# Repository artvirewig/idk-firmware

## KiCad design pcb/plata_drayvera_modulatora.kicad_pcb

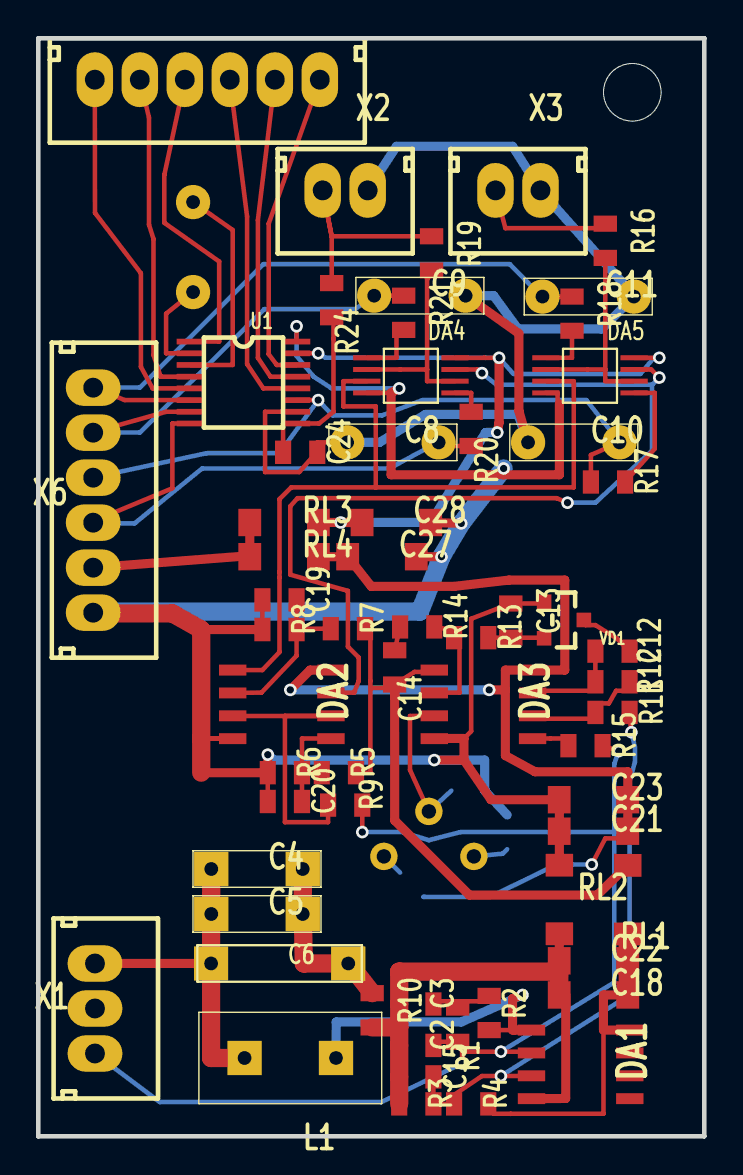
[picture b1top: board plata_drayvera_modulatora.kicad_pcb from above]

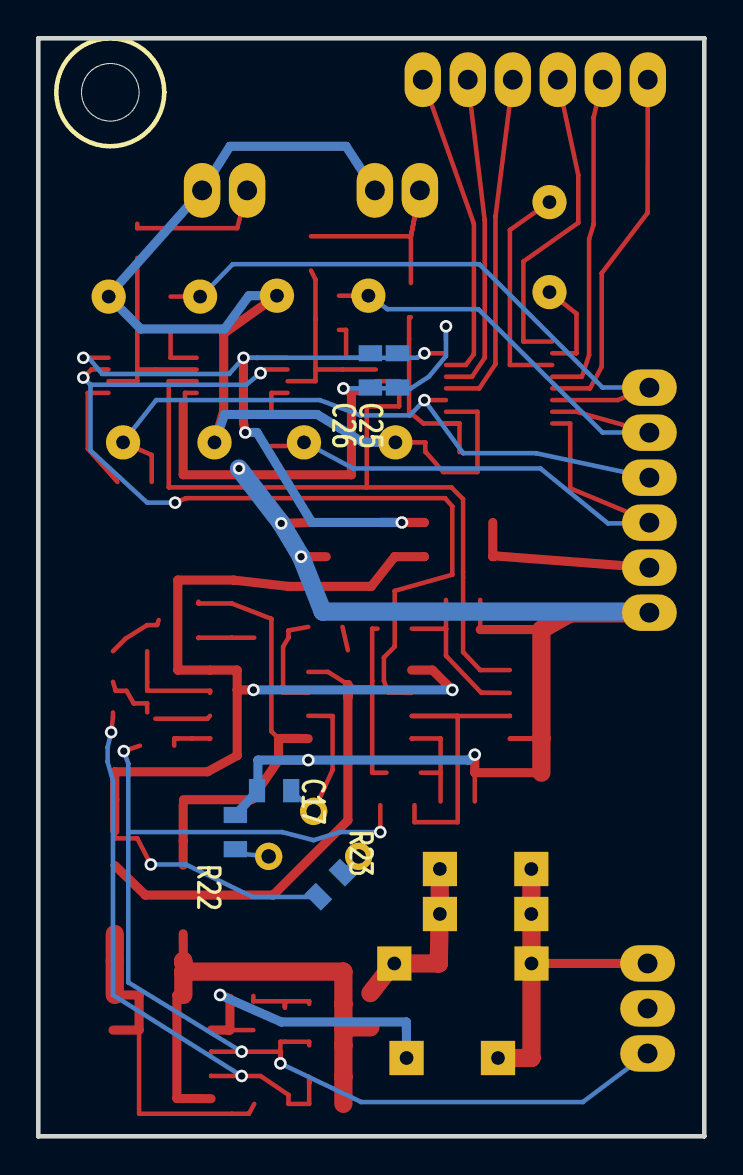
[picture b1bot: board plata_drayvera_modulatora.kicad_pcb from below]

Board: 2 copper layers, 37.0 x 61.0 mm, 66 parts (5 on the bottom side), 46 nets.

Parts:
C2, C14: 6n8; C0805_MINI_1
C3, C15, C17: 0.22; C0805_MINI_1
C4, C5, C8, C9, C10, C11: {Value}; C_1
C6: {Value}; C7_1
C12, C13, C19, C20, C24, C25, C26: 0.1; C0805_MINI_1
C18, C21, C22, C23, C27, C28: 10,0; C1206_1
DA1, DA3: AD8397_1_1
DA2: LMV762MA; AD8397_1_1
DA4, DA5: MAX4642_1
L1: RCH114NP-332KB; L-КИГ_1
R1, R24: 100k; R0805_MINI_1
R2: 51k; R0805_MINI_1
R3, R4, R5, R6, R7, R8, R9, R13, R14, R15, R16, R17, R18, R19, R20, R21, R22, R23: 1k; R0805_MINI_1
R10: 1R0; R0805_MINI_1
R11: 11k; R0805_MINI_1
R12: 22k; R0805_MINI_1
RL1, RL2, RL3, RL4: {Value}; R1206_1
U1: AD7705_1
VD1: BAT54S_1
X1: PW10-3-M_1
X2, X3: PW10-2-M_1
X5, X6: PW10-6M_1

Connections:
1:Z+I: R19.2, R24.1, X2.1
1_V+: C25.2, C26.2, C28.2, DA4.8, DA5.8, RL3.2, U1.15
2_V+: C21.1, C23.1, C27.2, DA2.8, DA3.8, R23.2, RL4.2
AGND: C8.1, C9.2, C10.1, C11.2, C24.1, U1.10, X2.2, X3.2
CS: U1.4, X5.2
DIN: U1.14, X5.6
DMD1+: C9.1, R21.2, U1.7, X6.5
DMD1-: C8.2, R20.2, U1.8, X6.3
DMD2+: C11.1, R18.2, U1.6, X6.6
DMD2-: C10.2, R17.2, U1.11, X6.4
DOUT: U1.13, X5.5
DRDY: U1.12, X5.4
GND: C13.2, C17.2, C19.2, C20.2, C21.2, C23.2, C25.1, C26.1, C27.1, C28.1, DA2.4, DA3.4, DA4.4, DA5.4, R6.1, R8.1, R22.2, RL2.2, U1.16, VD1.1, X6.1
HI_COMP: C20.1, DA2.5, R5.1, R6.2
LO_COMP: C19.1, DA2.2, R7.1, R8.2
NET00000: DA1.1, L1.1, R2.1
NET00001: C4.2, C5.2, C6.1, L1.2, X1.3
NET00002: C2.1, DA1.2, R1.2, R9.1, R15.1, X1.1
NET00003: C3.1, R1.1, R2.2
NET00005: C4.1, C5.1, C6.2, R10.2
NET00007: DA4.5, R20.1
NET00011: DA4.1, R21.1
NET00012: DA5.5, R17.1
NET00013: DA5.1, R18.1
NET00016: DA4.2, DA4.6, R19.1
NET00017: DA5.2, DA5.6, R16.1
NET00018: C12.1, DA3.7, R12.1
NET00019: C12.2, VD1.3
NET00020: C13.1, R13.1, VD1.2
NET00021: DA3.6, R11.2, R12.2
NET00022: DA3.2, R13.2, R14.1
NET00023: R16.2, X3.1
NET00024: C14.1, R14.2
NET00025: DA3.5, R15.2
NET00029: C14.2, DA3.1, R5.2, R7.2, RL1.1
NET00031: C24.2, R24.2, U1.9
REF_0: C15.1, DA1.3, R3.2, R4.1, R11.1
REF_PEM: C17.1, DA3.3
RESET: U1.5, X5.1
SCLK: U1.1, X5.3
SGND: C2.2, C3.2, C15.2, C18.2, C22.2, DA1.4, R3.1, R10.1, RL2.1
SIN_COMP: DA2.3, DA2.6, R9.2
SYNC_0: DA2.7, DA4.7, DA5.7
SYNC_1: DA2.1, DA4.3, DA5.3
V+: RL3.1, RL4.1, X6.2
V+REG: C18.1, C22.1, DA1.8, R4.2, RL1.2

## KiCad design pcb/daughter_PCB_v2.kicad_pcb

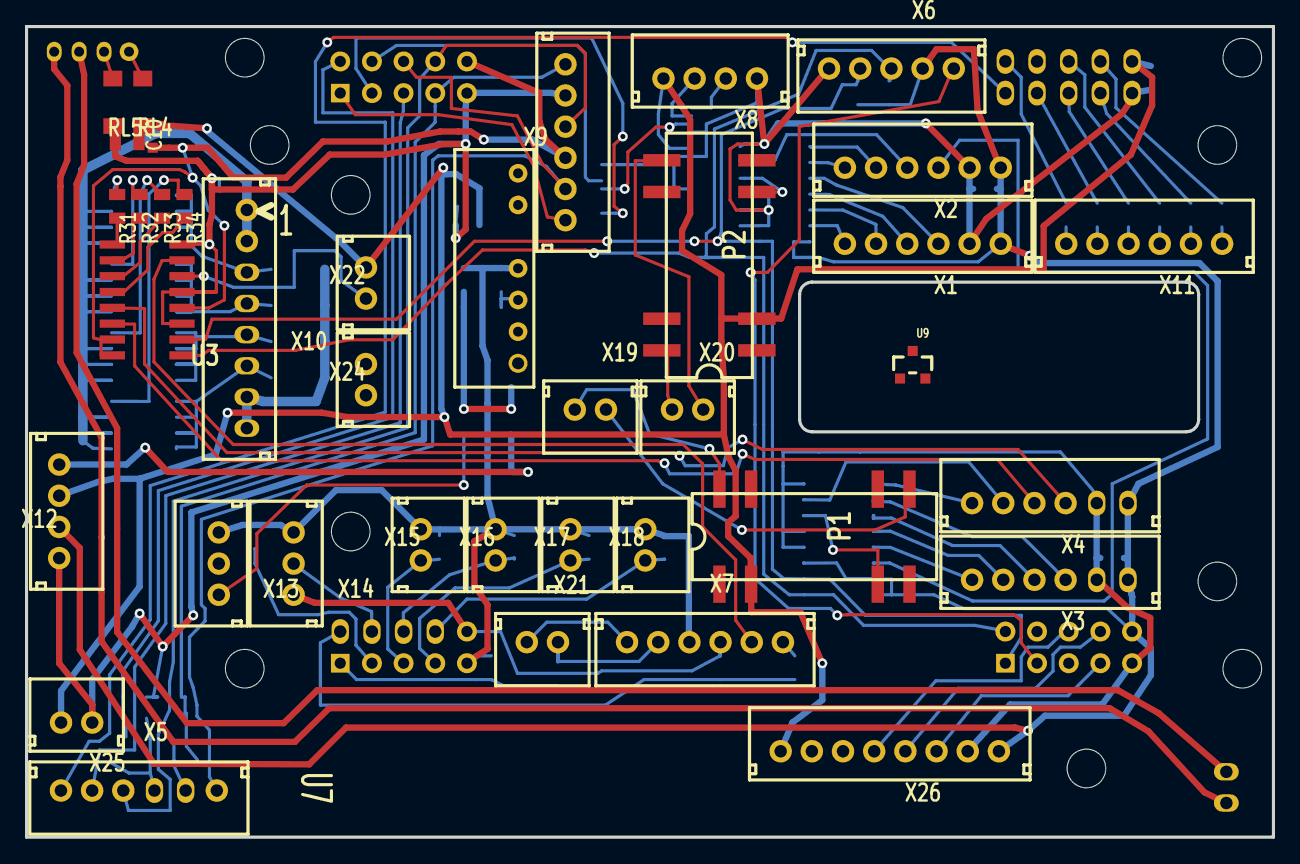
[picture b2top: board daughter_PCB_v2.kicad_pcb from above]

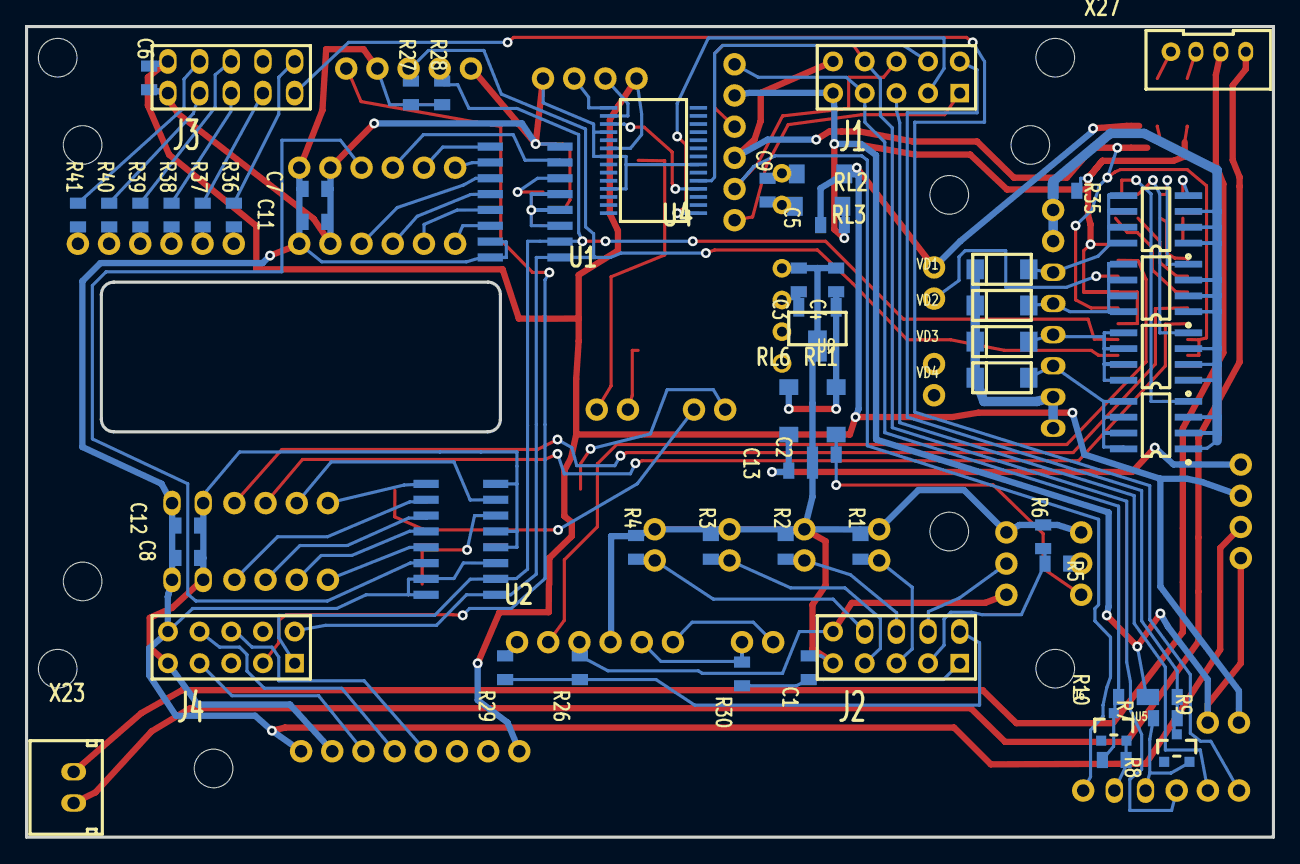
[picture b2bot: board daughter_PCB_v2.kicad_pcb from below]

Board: 2 copper layers, 100.0 x 65.0 mm, 95 parts (54 on the bottom side), 97 nets.

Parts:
C1, C2, C3, C4, C5, C6, C7, C8, C9, C10, C11, C12, C13: 0.22; C0805_MINI_1
J1, J2, J3, J4: PBD10_1
P1, P2: TRR1AS00D; TRR1A_1
R1, R2, R3, R4: k10; R0805_MINI_1
R5: 10k; R0805_MINI_1
R6, R27, R28, R36, R37, R38, R39, R40, R41: 3k3; R0805_MINI_1
R7, R8: 2k2; R0805_MINI_1
R9, R10: 4k7; R0805_MINI_1
R26: 300k; R0805_MINI_1
R29: 9M1; R0805_MINI_1
R30, R31, R32, R33, R34: 10K; R0805_MINI_1
R35: 10; R0805_MINI_1
RL1, RL2, RL3, RL4, RL5, RL6: 1206; R1206_1
U1, U2, U3: PCA9557_1
U4: FT232RL_1
U5, U6, U9: BAT54S_1
U7: {Value}; AMXD-XXXXD_1
U8: NJM78L09UA_1
VD1, VD2, VD3, VD4: VS-10MQ040; DIOD_SMA_1
VT1, VT2, VT3, VT4: IRF7416_1
X1: SERVO_1; PW10-6M_1
X2: SERVO_2; PW10-6M_1
X3: SERVO_3; PW10-6M_1
X4: SERVO_4; PW10-6M_1
X5: ADC; CONNECTOR_6_1
X6: BMP085; PW10-5-M_1
X7: PMT_BOARD; CONNECTOR_6_1
X8: USB; CONNECTOR_4_1
X9: SD card; PW10-6M_1
X10, X26: PW10-8M_1
X11: RESERVE; PW10-6M_1
X12: POWER IN; PW10-4-M_1
X13: Flow_sensor; PW10-3-M_1
X14: Cell T sensor; PW10-3-M_1
X15, X16, X17, X18, X19, X20, X21, X22, X23, X24, X25: PW10-2-M_1
X27: MU-4_1

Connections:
+: C10.1, RL4.2
+3.3: C7.1, C8.1, C11.1, C12.1, J1.10, J4.10, R27.2, R28.2, U1.15, U1.16, U2.3, U2.15, U2.16, U3.4, U3.15, U3.16, X1.1, X2.1, X3.1, X4.1, X6.4, X9.3, X12.2, X26.1
+5V: C5.1, C6.1, J3.10, P1.2, P2.2, RL2.1, U4.20, X8.4, X12.3, X22.2, X25.2, X26.8
+12: C13.1, RL6.2, X12.4
+12V: C4.1, RL1.1, RL6.1, U8.3
ADCA1: J3.2, R36.1
ADCA2: J3.3, R37.1
ADCB4: J3.5, R38.1
ADCB5: J3.6, R39.1
ADCB6: J3.7, R40.1
ADCB7: J3.8, R41.1
CLK: J1.8, X5.3, X9.4
CS_AD7705: J1.5, X5.2
CS_SD-CARD: J1.1, X9.1
DOUT_AD7705: R8.1, U6.2, X5.5
DRDY_AD7705: R7.1, U5.2, X5.4
GND: C1.2, C2.1, C3.2, C4.2, C5.2, C6.2, C7.2, C8.2, C10.2, C11.2, C12.2, C13.2, J1.9, J2.9, J3.9, J4.9, R1.1, R2.1, R3.1, R4.1, R6.1, R9.2, R10.2, R35.1, RL3.1, RL5.2, U1.3, U1.4, U1.5, U1.8, U2.4, U2.5, U2.8, U3.3, U3.5, U3.8, U4.7, U4.18, U4.21, U4.25, U7.4, U8.2, X1.2, X2.2, X3.2, X4.2, X6.1, X7.3, X8.1, X9.5, X12.1, X13.1, X14.1, X15.2, X16.2, X17.2, X18.2, X25.1, X26.2
IGN+: X23.1, X27.3
IGN-: X23.2, X27.4
IGNITION: U3.7, X7.5
L+: RL4.1, X27.1
L-: RL5.1, X27.2
MISO: J1.7, R8.2, R10.1, U6.3, X9.6
MOSI: J1.6, X5.6, X9.2
NET00000: R36.2, X11.6
NET00001: VD1.1, VD2.1, VD3.1, VD4.1, X10.7, X10.8
NET00002: C9.1, RL2.2, U7.1
NET00003: C9.2, RL3.2, U7.2
NET00004: R37.2, X11.5
NET00005: R38.2, X11.4
NET00006: C3.1, U7.5, U8.1
NET00007: R39.2, X11.3
NET00008: R40.2, X11.2
NET00009: R41.2, X11.1
NET00043: C1.1, J2.1, R30.1
NET00045: R5.1, X13.2
NET00046: J2.4, X14.2
NET00047: J2.5, R1.2, X15.1
NET00048: J2.6, R2.2, X16.1
NET00049: J2.7, R3.2, X17.1
NET00050: J2.8, R4.2, X18.1
NET00065: J4.3, X6.5
NET00066: U4.4, U4.17
NET00067: U4.16, X8.3
NET00068: U4.15, X8.2
NET00071: P2.6, U1.6
NET00072: P1.6, U2.6
NET00074: R29.2, X7.6
NET00075: P1.14, X19.1
NET00076: P1.8, X19.2
NET00077: P2.14, X20.1
NET00078: P2.8, X20.2
NET00079: R30.2, X7.2, X21.2
NET00080: X7.1, X21.1
NET00081: J2.3, R5.2, R6.2
NET00082: U3.6, X22.1
NET00083: R31.1, VT1.4
NET00084: R32.1, VT2.4
NET00085: R33.1, VT3.4
NET00086: R34.1, VT4.4
NET00087: R31.2, U3.9
NET00088: R32.2, U3.10
NET00089: R33.2, U3.11
NET00090: R34.2, U3.12
NET00091: VD4.2, VT4.5, VT4.6, VT4.7, VT4.8, X10.6
NET00092: VD3.2, VT3.5, VT3.6, VT3.7, VT3.8, X10.5
NET00093: VD2.2, VT2.5, VT2.6, VT2.7, VT2.8, X10.4
NET00094: VD1.2, VT1.5, VT1.6, VT1.7, VT1.8, X10.3
NET00095: R35.2, VT1.1, VT1.2, VT1.3, VT2.1, VT2.2, VT2.3, VT3.1, VT3.2, VT3.3, VT4.1, VT4.2, VT4.3, X10.1, X10.2
NET00105: C2.2, RL1.2, X13.3
PMT_V: J2.2, R26.1, R29.1
RESET: J3.1, X5.1
RXD_FT232: J1.4, U4.5
SCL: J4.2, R27.1, U1.1, U2.1, U3.1, X6.3
SDA: J4.1, R28.1, U1.2, U2.2, U3.2, X6.2
SERVO_1_DL<: U1.12, X1.4
SERVO_1_DR<: U1.11, X1.3
SERVO_1_L>: U1.14, X1.6
SERVO_1_R>: U1.13, X1.5
SERVO_2_DL<: U1.7, X2.4
SERVO_2_DR<: U2.14, X2.3
SERVO_2_L>: U1.10, X2.6
SERVO_2_R>: U1.9, X2.5
SERVO_3_DL<: U2.11, X3.4
SERVO_3_DR<: U2.10, X3.3
SERVO_3_L>: U2.13, X3.6
SERVO_3_R>: U2.12, X3.5
SERVO_4_DL<: U3.14, X4.4
SERVO_4_DR<: U3.13, X4.3
SERVO_4_L>: U2.9, X4.6
SERVO_4_R>: U2.7, X4.5
TXD_FT232: J1.3, U4.1
VCC_ANA_P3V3: J2.10, R26.2, X7.4, X14.3
_DRDY: J1.2, R7.2, R9.1, U5.3
_MISO: J4.7, X26.3
_MOSI: J4.6, X26.5
_SCK: J4.8, X26.4

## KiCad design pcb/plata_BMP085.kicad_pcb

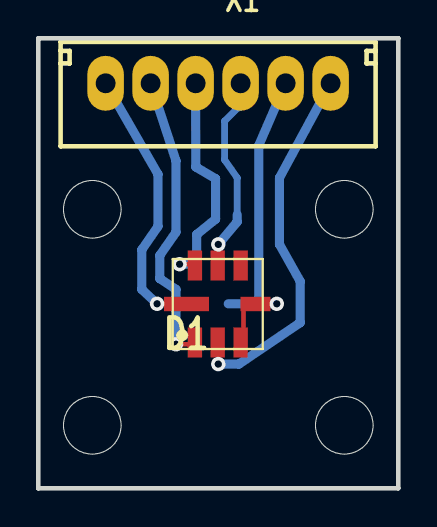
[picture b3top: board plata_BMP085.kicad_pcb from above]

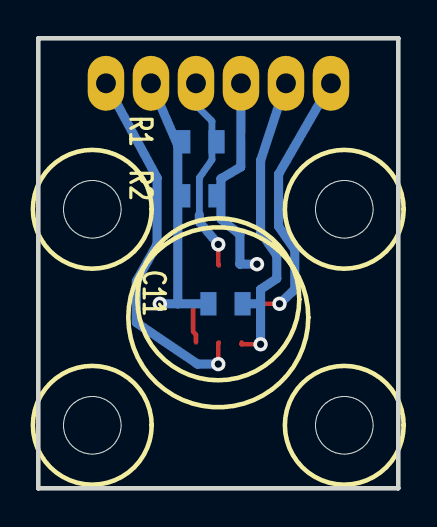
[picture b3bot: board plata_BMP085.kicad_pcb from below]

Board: 2 copper layers, 20.0 x 25.0 mm, 5 parts (3 on the bottom side), 6 nets.

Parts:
C11: 0.22; C0805_MINI_1
D1: BMP085_1
R1, R2: 10k; R0805_MINI_1
X1: PW10-6M_1

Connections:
EOC: D1.2, X1.6
GND: C11.2, D1.1, X1.2
MCLR: D1.8, X1.1
SCL: D1.6, R1.2, X1.4
SDA: D1.7, R2.2, X1.3
VDD: C11.1, D1.3, D1.4, R1.1, R2.1, X1.5

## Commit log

2016-01-02 pdf upload
2016-01-02 pcb upload
2016-01-02 atmel studio commit
2016-01-04 adc asf inject
2016-01-06 sensor fix
2016-01-06 avr upgrade
2016-01-06 asf upgrade
2016-01-06 atmel studio version downgrade
2016-01-15 project update
2016-01-15 makefile upload
2016-01-15 better days
2016-01-15 code upload
2016-01-15 gital
2016-01-15 what
2016-01-15 key fix
2016-01-15 asffxxxxx
2016-01-15 touch key
2016-01-15 touch enable
2016-01-17 add todo
2016-01-17 keyboard fix
2016-01-17 key bmp i2c float fix
2016-01-17 makefile fix
2016-01-17 gogogogo
2016-01-17 spidisplay
2016-01-17 serial printf enable
2016-01-18 xcode project
2016-01-18 median
2016-01-19 intera
2016-01-19 kaboom
2016-01-19 spincontrol
2016-01-19 displa
2016-01-19 fix proj
2016-01-20 serial keyboard input fix
2016-01-20 serial output
2016-01-20 gigno
2016-01-21 jkdsflsjdf
2016-01-22 adc calibration
2016-01-22 serial context
2016-01-22 header fix
2016-01-28 tweaks
2016-01-29 string display fix
2016-02-02 i2c fix
2016-02-02 fixiki
2016-02-15 adc test
2016-02-16 update this shit
